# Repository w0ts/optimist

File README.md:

<p align="center">
  <picture>
    <source media="(prefers-color-scheme: dark)" srcset="assets/logo/optimist-logo-on-dark.svg">
    <source media="(prefers-color-scheme: light)" srcset="assets/logo/optimist-logo-on-light.svg">
    
  </picture>
</p>

<h1 align="center">Optimist</h1>

<p align="center"><b>A modular firmware for the M-VAVE FM-1: pick what goes into your FM-1, build it in the browser, try it in
the browser, install it from the browser.</b><br>
Free software (GPL-3.0-only), built on <a href="https://github.com/isod89/sloop-fm1">SLOOP</a>, Felucca, Melodee, X0X and other
FM-1 projects (see <a href="#credits">Credits</a>).</p>

## What is in it

- **Four tracks:** three synth, drum with 10 lanes.
- **Many synth engines**
- Two LFOs and two envelopes per sound.
- **Drums:** sampled and synthesised kits, X0X 909 and 808.
- **Effects:** two insert slots on every track, three returns, punch-in effects.
- **Sequencer:** 64 steps a track, parameter locks, motion recording, chance and conditions, note generators, fills, patterns and scenes, undo.
- **Connections:**
  - **[JANK mode]([jank](https://github.com/w0ts/jank))**: Jam syned over Wi-Fi/Ableton Link with no router! 
  - **Ableton Link**, MIDI clock in/out
  - MIDI in: USB, TRS, Bluetooth
  - MIDI out: USB and Bluetooth
  - Bluetooth Audio
- **SD card mode:** projects, presets, kits and samples on a microSD card, samples streamed from it [the SD board](hardware/README.md)

## The flavours

Optimist is meant to be build using our web installer and customised to your needs. but we provide a few stock builds to try it out.

| Flavour | What it is |
| --- | --- |
| **mots-config** (the default) | My build|
| **synths** | Most of the synths |
| **synths-2** | What did not fit in **synths** build |
| **drum machine** | everything about drums, some synths. |

## Builder, Installer, editor [w0ts.github.io/optimist](https://w0ts.github.io/optimist/)

Use **Chrome or Edge** (they have Web MIDI) and a USB data cable, straight into the computer.

| | |
| --- | --- |
| [**Firmware**](https://w0ts.github.io/optimist/webapp/editor/#install) | Install a release flavour, your own build or a `.fwsc` file on your FM-1. It offers a backup first, and can put the official firmware back. **Build your own…** opens the builder: start from a flavour or a configuration you saved, choose the engines, drum kits, effects and features with a live flash and RAM budget, and press *Build* (no GitHub account needed). The page follows the build, then offers *Flash it* and *Try it in the simulator*. |
| [**Simulator**](https://w0ts.github.io/optimist/webapp/editor/#sim) | The firmware running in your browser, with the FM-1's panel and its keyboard shortcuts: try a build before you install it. It can copy your FM-1's memory in, and write it back. |
| [**Editor**](https://w0ts.github.io/optimist/webapp/editor/#mixer) | The **Backup** of your whole FM-1 in one file, the projects and presets librarian, and the FM-1's screen mirrored. A build with live editing (`ED_LIVE`, not in the four flavours) adds every sound, drum, effect and setting as knobs, the drum grid and the samples (with CHOP). |

The firmware files are also on the [releases page](https://github.com/w0ts/optimist/releases).

**Optimist Mirror**, the app: the FM-1's screen and panel on your iPhone, iPad or Mac, over USB or Bluetooth, and firmware installs.

## Your first install

1. **Back up.** Open the [Editor](https://w0ts.github.io/optimist/webapp/editor/#backup), *Connect*, then
   **Backup**: one `.optimist-backup` file with your projects, presets, kits and settings (tick *with the samples* for
   those too). Coming from another firmware, use its own backup as well.
2. Open [Install](https://w0ts.github.io/optimist/webapp/editor/#install): **Connect** says what your FM-1 runs,
   **Choose** a release and a flavour (or your cloud build, or a file), **Install** and wait for *Done*.
3. The FM-1 restarts into Optimist. If an install is cut off, the FM-1 stays in update mode: press Install again.

Your projects, presets, kits and samples live above the firmware: an install writes only the firmware area. Data that
Optimist cannot read may not be kept, except SLOOP's: SLOOP 2.7 data is kept.

## The guide

| | |
| --- | --- |
| [The interface](docs/guide/interface.md) · [every shortcut](docs/guide/shortcuts.md) | the controls, pages, settings and read-outs |
| [Sound](docs/guide/sound.md) · [Drums](docs/guide/drums.md) | the engines, voices, modulation and presets · kits, drum sounds, your samples and kits |
| [Effects](docs/guide/effects.md) · [Sequencer](docs/guide/sequencer.md) | inserts, sends, returns, the master · steps, locks, motion, patterns, the song |
| [MIDI, Bluetooth, USB audio, the web editor](docs/guide/midi-usb.md) | connections and the editor |
| [Getting back](docs/guide/getting-back.md) | to the official firmware, and what to do when the FM-1 does not start |
| [The builder](docs/BUILDER.md) | every builder item, its cost, the profiles |

## Build it on your computer

For developers, or to build without the cloud: macOS arm64 or Linux x86-64, Python 3.11+ (the compiler, pi32v2-llvm,
runs natively on both; other hosts build it first: BUILDING.md).

```
git clone https://github.com/w0ts/optimist.git && cd optimist
make setup      # fetch the toolchain, the SDK files and the builder's Python packages
make builder    # the builder in the terminal: pick, see the budget, build
make web        # the same site on your machine (installer, editor, simulator)
make test       # the host tests
```

[BUILDING.md](BUILDING.md) has the details: profiles, the emulator (`make emu`), the simulator, flashing from the command
line (`make flash`), releases and the site. The toolchain and SDK files are downloaded from JieLi and checked by SHA-256;
they are not in this repository.

## Credits

Optimist stands on other people's work. Each ported part is marked in its source files, keeps its authors' notice, and is
listed with its licence and commit in [LICENSING.md](LICENSING.md).

- **[SLOOP](https://github.com/isod89/sloop-fm1)** by isod89 and contributors: the base of this firmware; Erick Buendia Barrientos (Erbubar23); [renebohne's SLOOP fork](https://github.com/renebohne/sloop-fm1).
- **[Felucca](https://github.com/hugelton/Felucca)** by Leo Kuroshita (@kurogedelic), Hügelton Instruments: the platform, engines, sequencer, editor and installer SLOOP is built on, and many later features; [Felucca-Engines](https://github.com/hugelton/Felucca-Engines); [CrispyZebra](https://github.com/hugelton/CrispyZebra).
- **[Melodee](https://github.com/keremimo/melodee)** by Kerem Kilic (Ellic Studio) and contributors: FM6, CZ, the PROPHET voice, USB audio, TRS MIDI in, clock follow, MIDI expression, inserts, the rescue tool's checks, the second core's fault handling.
- **[Clipper](https://github.com/isod89/clipper-fm1)** by 3dSam: the STRINGS, VPS, TERRAIN, WSEQ, VECTOR and WAVE engines.
- **[Mini-Tone](https://github.com/eldontyrellcorp/Mini-Tone)** by Stephane Schmitz: the SID engine (after reSID 0.16 by Dag Lem).
- **[CS-1](https://github.com/twochannels/CS-1)** by twochannels: the CS80 engine's voice design.
- **[X0X](https://github.com/charlesvestal/fm1-x0x)** by Charles Vestal: the rescue tool, the ACID engine (Open303, TB-3PO), the X0X 909 / 808 kits (9W9, 8W8 by athousanddetails, ER-99 by Matthew Cieplak), the mixer glides, the second core's start.
- **[Flowstate](https://github.com/zakariachowdhury/flowstate-fm1)** by Zakaria Chowdhury: the performance macros, the CPU guard. **[Jangada](https://github.com/zednaked/jangada)** by zednaked: the SUPER engine, the second core's supply settings. **[Caravel](https://github.com/bonszaimusic/caravel)** by bonszaimusic: the DRONE engine's coupled network. **[fm-106](https://github.com/PatttF/fm-106)** by PatttF, after [Ultramaster KR-106](https://github.com/kayrockscreenprinting/ultramaster_kr106): the JUNO engine and chorus.
- DaisySP, Rings, Plaits, MAME's uPD933, Airwindows, MSFA and Dexed, sc808; samples from Versilian Studios and Sonic Pi (CC0); fonts Terminus and JetBrains Mono (SIL OFL), Fukiai (MIT); [fm1-emulator](https://github.com/simonjohansson/fm1-emulator) by Simon Johansson; [jl-uboot-tool](https://github.com/kagaimiq/jl-uboot-tool) by kagaimiq; [M-Flasher](https://github.com/jvitkauskas/m-flasher) and [m-bootloader](https://github.com/jvitkauskas/m-bootloader) by Julius Vitkauskas: download-mode installs and the open bootloader ([docs/INSTALL-PATHS.md](docs/INSTALL-PATHS.md)).

Unofficial: not made, endorsed or supported by M-VAVE. M-VAVE and FM-1 are trademarks of their owners. Product names
(Juno-106, TB-303, TR-808, TR-909, DX7, CZ, Prophet-5, Prophet VS, Wavestation, SID) only say what an engine or kit models.

## Licence and contributing

Code: **GPL-3.0-only** ([LICENSE](LICENSE)), the Bluetooth stack and the Wi-Fi code GPL-3.0-only OR MPL-2.0 (the Ableton Link port stays GPL-3.0-only); assets have their own terms ([LICENSING.md](LICENSING.md)). No warranty. If
you distribute a build, give its source under the same licence.

To add an engine, an effect, a note generator or a UI change, read [CONTRIBUTING.md](CONTRIBUTING.md): where the code
lives, how a piece becomes a builder item, three worked examples in the tree, and how to open a pull request.

Issues and pull requests: [github.com/w0ts/optimist](https://github.com/w0ts/optimist). A useful report names the build
(the flavour and release, or the cloud build's id), says whether it happened in the simulator, the emulator or on an
FM-1, and how to reproduce it. Run `make test` before sending a change, and keep each ported part marked with its source
and licence.

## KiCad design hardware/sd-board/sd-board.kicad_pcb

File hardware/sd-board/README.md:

The KiCad files. `make_board.py` draws the board; `sh make_fab.sh` writes `fab/`.

How to order: [`../README.md`](../README.md). Design notes: [`../research/sd-board-design.md`](../research/sd-board-design.md).

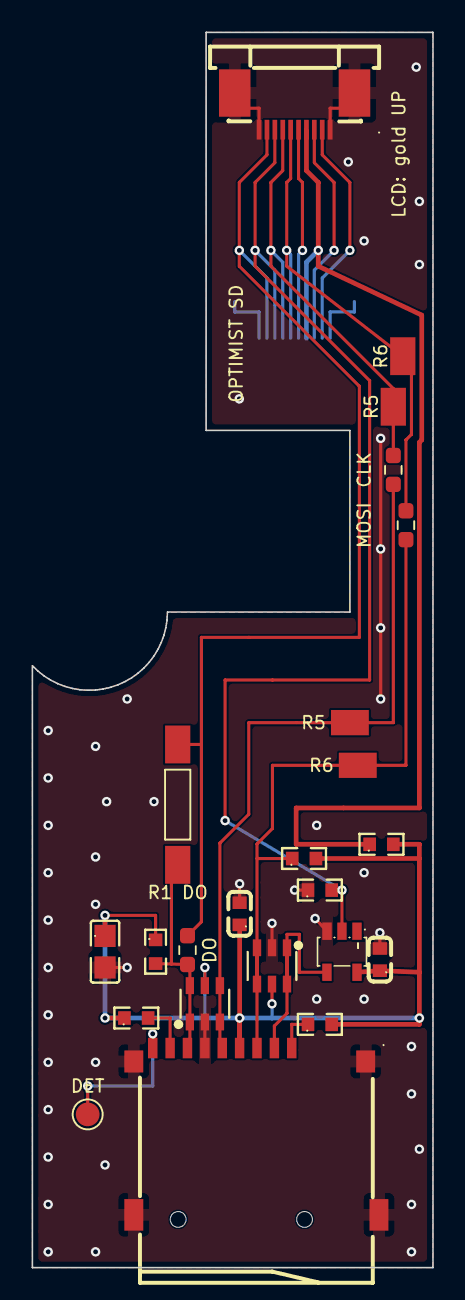
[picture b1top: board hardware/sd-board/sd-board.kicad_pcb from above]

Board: 2 copper layers, 25.4 x 78.2 mm, 22 parts (1 on the bottom side), 17 nets.

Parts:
C1: 10uF; C0805
C2, C3: 100nF; C0603
FB1: 600R@100MHz; R0603
J1: TF-01A push-push; TF-SMD_TF-01A
J2, J3: FPC 10P 0.5mm top contact; FPC-SMD_10P-P0.50_XUNPU_FPC-0.5AS-10PWBH20
R1: 120; R_0603_1608Metric_Pad0.98x0.95mm_HandSolder
R2, R3, R4, R7, R8: 47k; R0603
R5, R6: 270; R_0603_1608Metric_Pad0.98x0.95mm_HandSolder
RT1: parallel to R1; R_twin_P7.62
RT5: parallel to R5; R_twin_RT5
RT6: parallel to R6; R_twin_RT6
TP5: J12 DET; TestPoint_Pad_D1.5mm
U1: 74LVC1G04; SOT-23-5_L3.0-W1.7-P0.95-LS2.8-BR
U2, U3: USBLC6-2SC6; SOT-23-6_L2.9-W1.6-P0.95-LS2.8-BL

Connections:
3V3: FB1.1, J2.7, J3.4
CARD_CS: J1.2, U1.4, U2.1, U2.6
CARD_DET: J1.9, TP5.1
CLK: J2.4, J3.7, R5.2, RT5.1
CLK_SD: J1.5, R5.1, RT5.2, U3.3, U3.4
DAT0: J1.7, R1.2, R7.2, RT1.1, U3.1, U3.6
DAT1: J1.8, R3.2
DAT2: J1.1, R2.1
GND: C1.2, C2.2, C3.2, J1.6, J1.10, J1.11, J1.12, J1.13, J2.1, J2.10, J2.11, J2.12, J3.1, J3.10, J3.11, J3.12, R4.1, U1.3, U2.2, U3.2
LCD_6: J2.6, J3.5
LCD_8: J2.8, J3.3
LCD_9: J2.9, J3.2
LCD_CS: J2.3, J3.8, R4.2, U1.2
MISO: J2.2, J3.9, R1.1, RT1.2
MOSI: J2.5, J3.6, R6.2, RT6.1
MOSI_SD: J1.3, R6.1, R8.1, RT6.2, U2.3, U2.4
SD_VDD: C1.1, C2.1, C3.1, FB1.2, J1.4, R2.2, R3.1, R7.1, R8.2, U1.5, U2.5, U3.5

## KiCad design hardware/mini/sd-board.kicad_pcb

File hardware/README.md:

# SD card for the FM-1

A small board that adds a microSD slot to the M-VAVE FM-1. **No soldering on the FM-1:** it plugs in between the LCD
cable and the main board.

## What it brings to Optimist

- Projects, presets, kits and samples on the card.
- Samples streamed from the card: 8 voices at once, measured on an FM-1.
- Browse the card's samples on the FM-1.
- More room for code: your data leaves the FM-1's flash.
- Install firmware from the card with [m-bootloader](https://github.com/jvitkauskas/m-bootloader).

Turn on **SD card mode** in the builder. If the screen stays black with the board in, build with `LCD_BAUD=1`
(screen at 30 MHz).

> **Not built yet:** this board is not tested, and its resistor values may still change. The board before it
> ([`research/archive-v6-tested/`](research/archive-v6-tested/)) runs in an FM-1.

## Order it on JLCPCB

1. Download [`sd-board-gerbers.zip`](https://github.com/w0ts/optimist/raw/main/hardware/sd-board/fab/sd-board-gerbers.zip)
   and upload it on [jlcpcb.com](https://jlcpcb.com).
2. Change these settings. Leave the rest at the defaults.

   | Setting | Value |
   |---|---|
   | Layers | 2 |
   | Thickness | 1.6 mm |
   | Surface finish | HASL |
   | PCB Assembly | On, Standard, **Both Sides** |
   | BOM | [`bom.csv`](https://github.com/w0ts/optimist/raw/main/hardware/sd-board/fab/bom.csv) |
   | Pick and place | [`cpl.csv`](https://github.com/w0ts/optimist/raw/main/hardware/sd-board/fab/cpl.csv) |

3. In the preview, check J2 sits on the bottom side.

Also buy a [10-pin, 0.5 mm FFC cable](https://www.aliexpress.com/item/4000022050815.html) (type A, about 80 mm) and a microSD card.

## Fit it

1. Print the tray, [`tray/sd-tray.stl`](tray/sd-tray.stl).
2. Cut a 15 x 2.5 mm slot in the case's bottom wall, 81.7 mm from the left wall's inside.
3. Cut the plastic under the audio jacks, so the ribbon cable can pass.
4. Battery off. Board into the tray, right of the battery.
5. LCD cable into **J3**, gold up. The new cable from J12 into **J2**, gold down.

## Folders

- [`sd-board/`](sd-board/): the KiCad board and the order files.
- [`tray/`](tray/): the printed tray.
- [`research/`](research/): measurements, bench tests, older boards.

Based on [m-card](https://github.com/jvitkauskas/m-card) by Julius Vitkauskas (CC0).

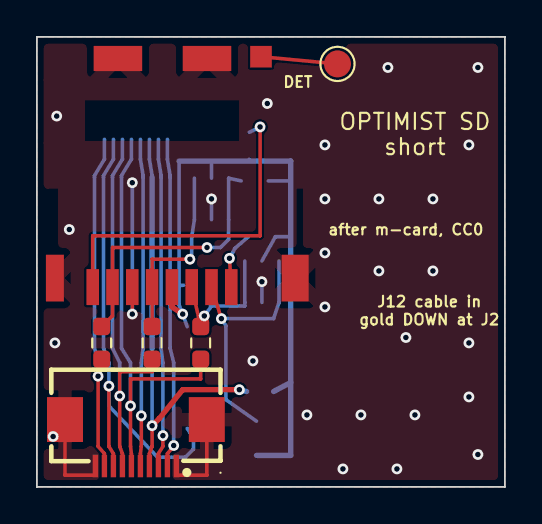
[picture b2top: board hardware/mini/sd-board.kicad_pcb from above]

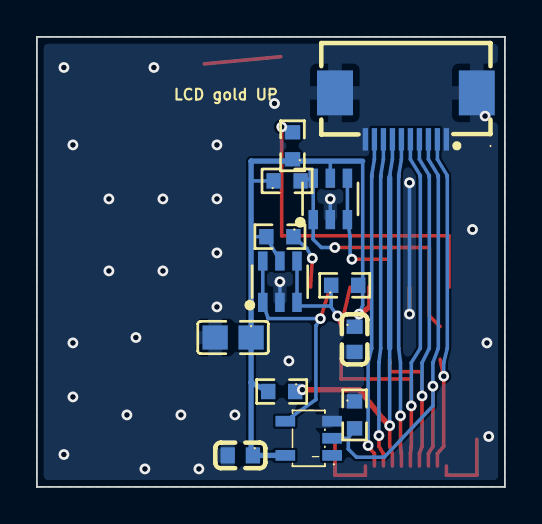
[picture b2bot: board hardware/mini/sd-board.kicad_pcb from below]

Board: 2 copper layers, 26.0 x 25.0 mm, 19 parts (13 on the bottom side), 17 nets.

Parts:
C1: 10uF; C0805
C2, C3: 100nF; C0603
FB1: 600R@100MHz; R0603
J1: DM3CS-SF hinged; microSD_Hirose_DM3CS-SF_hinged
J2, J3: FPC 10P 0.5mm bottom contact; FPC-SMD_10P-P0.50_XUNPU_FPC-05F-10PH20
R1: 91; R_0603_1608Metric_Pad0.98x0.95mm_HandSolder
R2, R3, R4, R7, R8: 47k; R0603
R5, R6: 240; R_0603_1608Metric_Pad0.98x0.95mm_HandSolder
TP5: J12 DET; TestPoint_Pad_D1.5mm
U1: 74LVC1G04; SOT-23-5_L3.0-W1.7-P0.95-LS2.8-BR
U2, U3: USBLC6-2SC6; SOT-23-6_L2.9-W1.6-P0.95-LS2.8-BL

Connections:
3V3: FB1.1, J2.4, J3.7
CARD_CS: J1.2, U1.4, U2.1, U2.6
CARD_DET: J1.9, TP5.1
CLK: J2.7, J3.4, R5.2
CLK_SD: J1.5, R5.1, U3.3, U3.4
DAT0: J1.7, R1.2, R7.2, U3.1, U3.6
DAT1: J1.8, R3.2
DAT2: J1.1, R2.1
GND: C1.2, C2.2, C3.2, J1.6, J1.10, J1.11, J1.12, J1.13, J2.1, J2.10, J2.11, J2.12, J3.1, J3.10, J3.11, J3.12, R4.1, U1.3, U2.2, U3.2
LCD_6: J2.5, J3.6
LCD_8: J2.3, J3.8
LCD_9: J2.2, J3.9
LCD_CS: J2.8, J3.3, R4.2, U1.2
MISO: J2.9, J3.2, R1.1
MOSI: J2.6, J3.5, R6.2
MOSI_SD: J1.3, R6.1, R8.1, U2.3, U2.4
SD_VDD: C1.1, C2.1, C3.1, FB1.2, J1.4, R2.2, R3.1, R7.1, R8.2, U1.5, U2.5, U3.5

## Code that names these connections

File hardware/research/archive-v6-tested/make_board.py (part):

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
Then make_fab.sh checks it (DRC, the schematic's nets) and writes the JLCPCB files (Gerbers, drill, BOM, placement).

Nets (microSD pins: 1 DAT2, 2 DAT3/CS, 3 CMD, 4 VDD, 5 CLK, 6 VSS, 7 DAT0, 8 DAT1, 9 card detect, 10-13 shell;
v6: J2 (IN, from J12) and J3 (the LCD's cable), 10 pins each, every line through, J12 pin n = J2's and J3's n-th
contact from the left (both turned: their own numbering runs the other way, J2_AT, J3_AT);
J12's pin map as Julius probed it, 2026-10-27, docs/SD-CARD-DESIGN.md section 3; pin 7's 3.3 V confirmed 2026-10-28; J12 counts from the right):
  GND      J2 1, 10 -> J1 6, the shell, U1 GND, R4, the sockets' tabs
  MISO     J2 2 (PC8, the LCD's D/C) -> R1 220 -> J1 7 (DAT0): R1 takes any overlap with the D/C drive; R7 47k
           pulls DAT0 up at the card (an empty slot reads 0xFF without PC8's own pull-up)
  LCD_CS   J2 3 (PC7) -> U1 A (74LVC1G04 in); R4 47k pull-DOWN (the card deselected while the FM-1 resets)
  CLK      J2 4 (PC9) -> R5 510 -> CLK_SD -> J1 5
  MOSI     J2 5 (PC10) -> R6 510 -> MOSI_SD -> J1 3 (CMD)
  3V3      J2 7 -> (JP5) SD_VIN -> FB1 ferrite -> SD_VDD: J1 4, C3 100 nF by it, U1 VCC, C1 10 uF, C2 100 nF, the
           pull-ups (the card's hot insertion kept off the LCD's rail: Julius's review, 2026-10-28)
  CARD_CS  U1 Y  -> J1 2
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                                                 # ohm, Julius's prototype: stock firmware's screen blank with a card in
                                                 # its native mode with CLK direct, distorted at 150, fine at 510)
# ESD at the card's contacts: two USBLC6-2SC6, each line straight through one of its columns (pins 1 and 6 are one
# line, 3 and 4 the other: flow-through, no stub); U3 on DAT0 and CLK with its GND pin right over the card's ground
# contact, U2 on CMD (DI) and CS, turned so its VBUS pin sits over the bottom 3V3 bus
SOT6 = "SOT-23-6_L2.9-W1.6-P0.95-LS2.8-BL"
U3 = P(LIB, SOT6, "U3", "USBLC6-2SC6", 82.32, 14.2 + DY, 0, "C7519")
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# ---- the nets: J12's pin map as probed (Julius, 2026-10-27), the same on J2 and J3 (every line straight through, J3
# pin n = J2 pin n; the cable from J12 must arrive unmirrored: the breakout's check). Pin 7 is 3V3 (Julius's prototype
# runs the card from it, 2026-10-28); the swap block still lets any line be rewired by hand
LCD_PINS = {1: "GND", 2: "MISO", 3: "LCD_CS", 4: "CLK", 5: "MOSI", 6: "LCD_6", 7: "3V3", 8: "LCD_8",
            9: "LCD_9", 10: "GND", 11: "GND", 12: "GND"}
for num, name in ((1, "DAT2"), (2, "CARD_CS"), (3, "SD_DI"), (4, "SD_VDD"), (5, "SD_CLK"), (6, "GND"), (7, "DAT0"),
                  (8, "DAT1"), (9, "CARD_DET"), (10, "GND"), (11, "GND"), (12, "GND"), (13, "GND")):
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

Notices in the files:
hardware/research/archive-v6-tested/make_board.py:
SPDX-License-Identifier: GPL-3.0-only
(lib/stitch.py: after m-card's stitch(), CC0-1.0)
hardware/mini/sd-board.kicad_pcb:
after m-card, CC0
